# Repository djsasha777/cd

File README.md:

# apps manifests for code-build-deployments

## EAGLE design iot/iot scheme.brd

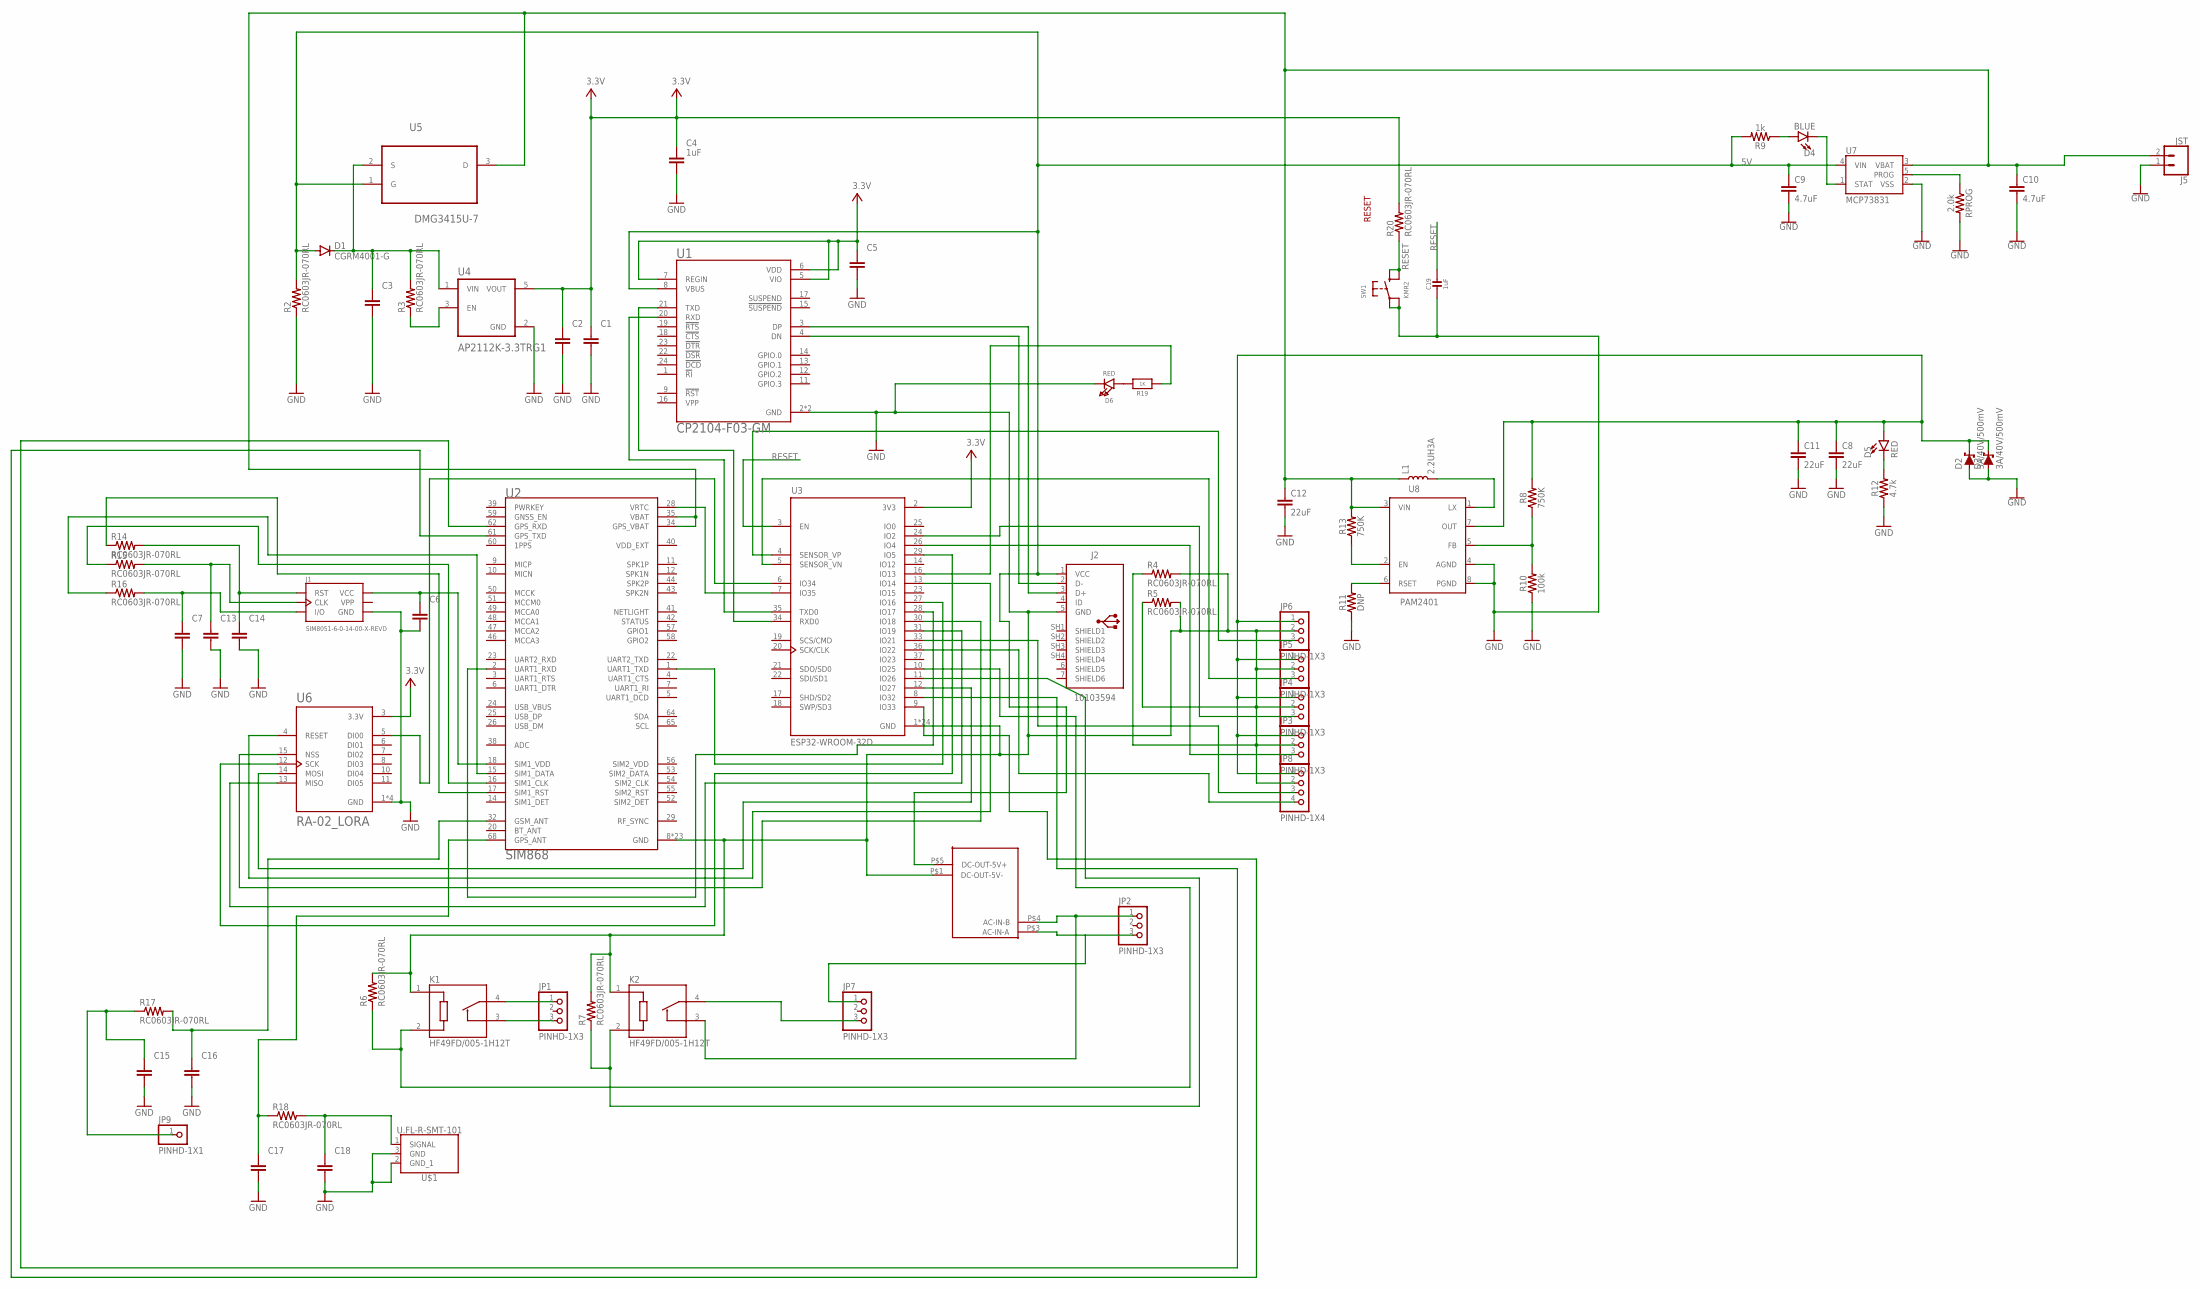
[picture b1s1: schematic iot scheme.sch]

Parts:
C1, C2, C3, C5, C6, C7, C13, C14, C15, C16, C17, C18: C_CHIP-0603(1608-METRIC); CAPC1608X85
C4: 1uF; CAPC1608X85
C8, C11, C12: 22uF; 0805
C9, C10: 4.7uF; 0603
C19: 1uF; 0603-NO
D1: CGRM4001-G; SOD-123_MINI-SMA
D2, D3: 3A/40V/500mV; SMA-DIODE
D4: BLUE; LED-0603
D5: RED; LED-0603
D6: RED; CHIPLED_0805_NOOUTLINE
J1: SIM8051-6-0-14-00-X-REVD; GCT_SIM8051-6-0-14-00-X-REVD
J2: 10103594
J5: JST; JST-2-SMD
JP1, JP2, JP3, JP4, JP5, JP6, JP7: PINHD-1X3; 1X03
JP8: PINHD-1X4; 1X04
JP9: PINHD-1X1; 1X01
K1, K2: HF49FD/005-1H12T; RELAY_HF49FD/005-1H12T
L1: 2.2UH3A; INDUCTOR_4X4MM
R1: AC-DC-5V; MYFOOT
R2, R3, R4, R5, R6, R7, R14, R15, R16, R17, R18, R20: RC0603JR-070RL; RES_0603
R8, R13: 750K; 0603
R9: 1k; 0603
R10: 100k; 0603
R11: DNP; 0603
R12: 4.7k; 0603
R19: 1K; 0603-NO
RPROG: 2.0k; 0603
SW1: KMR2; BTN_KMR2_4.6X2.8
U1: CP2104-F03-GM; QFN50P400X400X80-25N
U2: SIM868; XCVR_SIM868
U3: ESP32-WROOM-32D; MODULE_ESP32-WROOM-32D
U4: AP2112K-3.3TRG1; SOT95P285X140-5N
U5: DMG3415U-7; SOT95P240X105-3N
U6: RA-02_LORA; MODULE_RA-02_LORA
U7: MCP73831; SOT23-5
U8: PAM2401; MSOP8
U$1: U.FL-R-SMT-101; U.FL-R-SMT-1(XX)

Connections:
5V: C9.1, D1.A, J2.1 (VCC), R1.P$5 (DC-OUT-5V+), R2.2, R9.2, U1.8 (VBUS), U5.1 (G), U7.4 (VIN)
EN: R13.1, U8.2 (EN)
GND: C1.2, C2.2, C3.2, C4.2, C5.2, C6.2, C7.2, C8.2, C9.2, C10.2, C11.2, C12.2, C13.2, C14.2, C15.2, C16.2, C17.2, C18.2, C19.2, D2.A, D3.A, D6.C, J1.C5 (GND), J2.5 (GND), J5.1 (2), JP3.2, JP4.2, JP5.2, JP6.2, JP8.2, K1.1 (L1), K2.1 (L1), R1.P$1 (DC-OUT-5V-), R2.1, R4.1, R4.2, R5.1, R5.2, R6.2, R7.2, R10.1, R11.1, R12.1, RPROG.2, SW1.A, SW1.A' (P1), U1.2 (GND), U1.25 (GND), U2.8 (GND), U2.13 (GND), U2.19 (GND), U2.21 (GND), U2.27 (GND), U2.30 (GND), U2.31 (GND), U2.33 (GND), U2.36 (GND), U2.37 (GND), U2.45 (GND), U2.63 (GND), U2.66 (GND), U2.67 (GND), U2.69 (GND), U2.70 (GND), U2.71 (GND), U2.72 (GND), U2.73 (GND), U2.74 (GND), U2.75 (GND), U2.76 (GND), U2.77 (GND), U3.1 (GND), U3.15 (GND), U3.38 (GND), U3.39_1 (GND), U3.39_2 (GND), U3.39_3 (GND), U3.39_4 (GND), U3.39_5 (GND), U3.39_6 (GND), U3.39_7 (GND), U3.39_8 (GND), U3.39_9 (GND), U3.39_10 (GND), U3.39_11 (GND), U3.39_12 (GND), U3.39_13 (GND), U3.39_14 (GND), U3.39_15 (GND), U3.39_16 (GND), U3.39_17 (GND), U3.39_18 (GND), U3.39_19 (GND), U3.39_20 (GND), U3.39_21 (GND), U4.2 (GND), U6.1 (GND), U6.2 (GND), U6.9 (GND), U6.16 (GND), U7.2 (VSS), U8.4 (AGND), U8.8 (PGND), U$1.2 (GND_1), U$1.3 (GND)
unnamed: L1.P$2 (2), U8.1 (LX)
unnamed: J2.3 (D+), U1.3 (DP)
unnamed: J2.2 (D-), U1.4 (DN)
unnamed: R3.1, U4.3 (EN)
unnamed: U1.20 (RXD), U3.35 (TXD0)
unnamed: U1.21 (TXD), U3.34 (RXD0)
unnamed: C3.1, D1.C, R3.2, U4.1 (VIN), U5.2 (S)
unnamed: R11.2, U8.6 (RSET)
unnamed: JP2.1, K2.3 (C2), R1.P$4 (AC-IN-B)
unnamed: D5.C, R12.2
unnamed: RPROG.1, U7.5 (PROG)
unnamed: R8.1, R10.2, U8.5 (FB)
unnamed: D4.A, R9.1
unnamed: D4.C, U7.1 (STAT)
unnamed: JP2.3, JP7.1, R1.P$3 (AC-IN-A)
unnamed: JP1.1, K1.4 (C1)
unnamed: JP1.3, K1.3 (C2)
unnamed: JP7.3, K2.4 (C1)
unnamed: JP6.3, U3.4 (SENSOR_VP)
unnamed: D6.A, R19.2
unnamed: JP5.3, U3.5 (SENSOR_VN)
unnamed: JP8.3, U3.33 (IO21)
unnamed: JP8.4, U3.36 (IO22)
unnamed: JP4.3, U3.24 (IO2)
unnamed: JP3.3, U3.26 (IO4)
unnamed: U3.13 (IO14), U6.4 (RESET)
unnamed: K1.2 (L2), R6.1, U3.10 (IO25)
unnamed: K2.2 (L2), R7.1, U3.11 (IO26)
unnamed: U3.30 (IO18), U6.15 (NSS)
unnamed: U3.12 (IO27), U6.14 (MOSI)
unnamed: U3.31 (IO19), U6.13 (MISO)
unnamed: U3.29 (IO5), U6.12 (SCK)
unnamed: U3.6 (IO34), U6.5 (DI00)
unnamed: U2.1 (UART1_TXD), U3.27 (IO16)
unnamed: U2.2 (UART1_RXD), U3.28 (IO17)
unnamed: C6.1, J1.C1 (VCC), U2.18 (SIM1_VDD)
unnamed: R15.1, U2.16 (SIM1_CLK)
unnamed: R14.1, U2.17 (SIM1_RST)
unnamed: C14.1, J1.C2 (RST), R14.2
unnamed: C13.1, J1.C3 (CLK), R15.2
unnamed: C7.1, J1.C7 (I/O), R16.2
unnamed: R16.1, U2.15 (SIM1_DATA)
unnamed: C16.1, R17.2, U2.32 (GSM_ANT)
unnamed: C17.1, R18.1, U2.68 (GPS_ANT)
unnamed: C15.1, JP9.1, R17.1
unnamed: U2.28 (VRTC), U3.7 (IO35)
unnamed: C18.1, R18.2, U$1.1 (SIGNAL)
unnamed: C8.1, C11.1, D2.C, D3.C, D5.A, JP3.1, JP4.1, JP5.1, JP6.1, JP8.1, R8.2, U8.7 (OUT)
unnamed: U2.62 (GPS_RXD), U3.8 (IO32)
unnamed: R19.1, U3.16 (IO13)
unnamed: U2.61 (GPS_TXD), U3.9 (IO33)
RESET: C19.1, R20.1, SW1.B (S), SW1.B' (S1), U3.3 (EN)
V+: C1.1, C2.1, C4.1, C5.1, R20.2, U1.5 (VIO), U1.6 (VDD), U1.7 (REGIN), U3.2 (3V3), U4.5 (VOUT), U6.3 (3.3V)
VBATT: C10.1, C12.1, J5.2 (1), L1.P$1 (1), R13.2, U2.34 (GPS_VBAT), U2.35 (VBAT), U5.3 (D), U7.3 (VBAT), U8.3 (VIN)
VPP: J1.C6 (VPP)

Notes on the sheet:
RESET

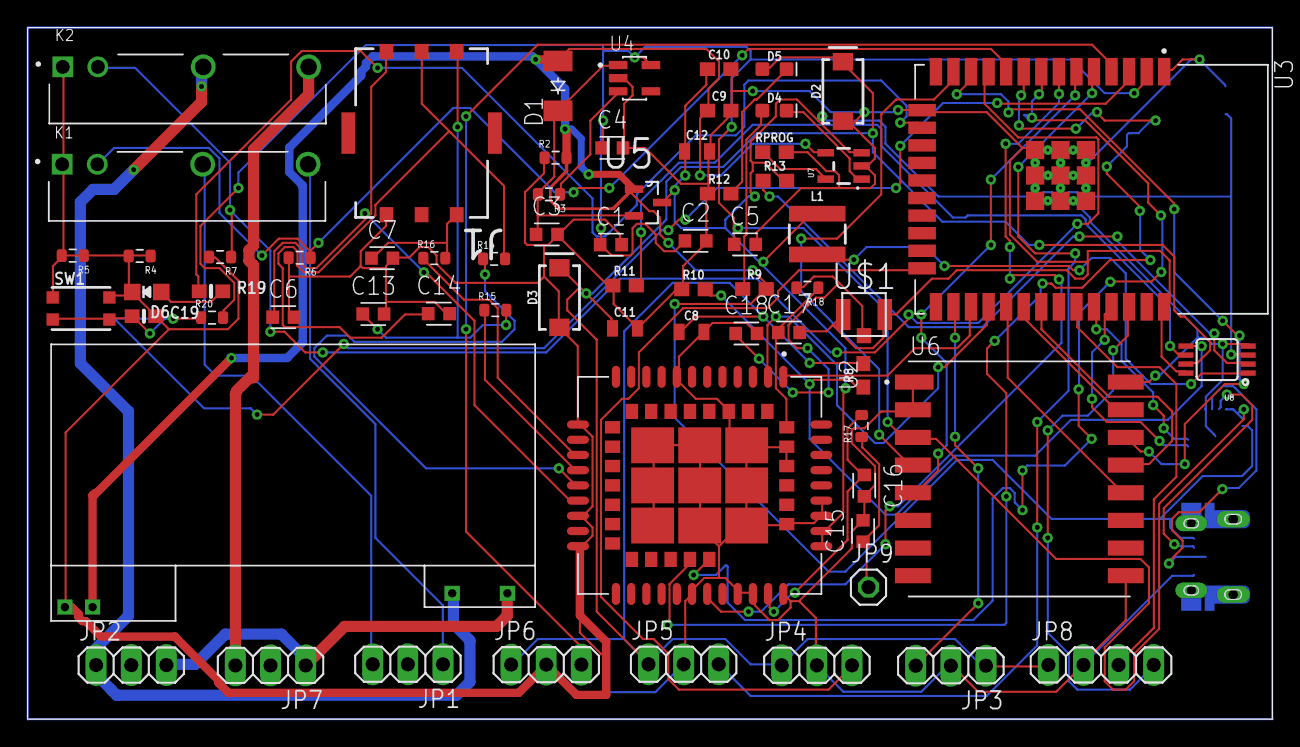
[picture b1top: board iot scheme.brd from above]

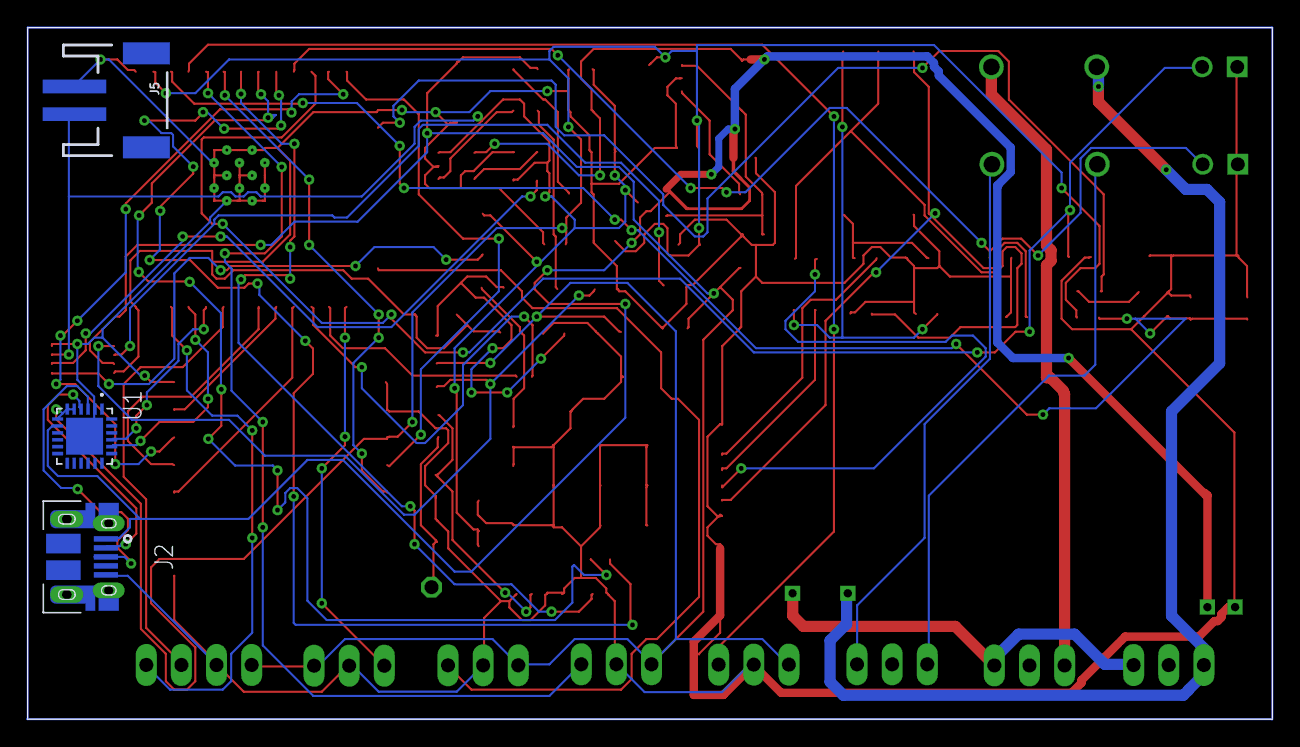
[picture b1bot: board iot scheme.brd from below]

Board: 2 copper layers, 90.0 x 50.0 mm, 71 parts (3 on the bottom side), 57 nets.

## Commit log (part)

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2021-11-15 Update README.md
    up
2021-11-15 Update README.md
    y
2021-11-26 up backend
2021-11-26 add jenkins only build and push file
2021-11-26 up version
2021-12-08 up to version 4
2021-12-08 up to version 5
2021-12-08 up to version 6
2021-12-09 up to version 7
2021-12-09 up ingress
2021-12-09 up ingress edit
2021-12-15 up add metrics
2021-12-15 up add metr
2021-12-15 up metrics
2021-12-17 clean
2022-03-05 Update iot-app.yaml
    up
2022-06-28 Create main.yml
    add actions
2022-07-05 change cname
2022-07-14 megaupp
2022-07-14 fix1
2022-07-14 fix2
2022-07-14 fix3
2022-07-14 fix4
2022-07-14 fix5
2022-07-14 fix6
2022-07-15 fix7
2022-07-15 fix8
2022-07-18 up234
2022-07-18 prod
2022-08-09 add nasos
2022-09-12 rename
2022-10-19 Update docker-compose.yaml
    u
2022-10-19 Create .gitlab-ci.yml
    add
2022-10-21 mega up
2023-10-22 up helm
2023-10-22 edit
2023-11-03 add xconsole
2024-09-10 Create CNAME
2024-09-10 add test helm
2024-09-19 istio
2025-06-15 occlient
2025-06-15 main
2025-09-11 test

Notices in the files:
parts and their libraries:
SparkFun-Capacitors: Licensing: CC v3.0 Share-Alike You are welcome to use this library for commercial purposes.
SparkFun-LED: Licensing: Creative Commons ShareAlike 4.0 International - https://creativecommons.org/licenses/by-sa/4.0
